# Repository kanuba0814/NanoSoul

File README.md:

# NanoSoul · ESP32-P4 桌面陪伴机器人

NanoSoul 是一台桌面陪伴机器人。它在本地检测人脸和环境，据此决定表情和动作；联网后可以进行语音对话。项目是团队参赛作品（2026 中国高校计算机大赛·人工智能创意赛），本仓库中的固件、测试上位机和文档由我提交。

当前实物是 **Waveshare ESP32-P4-WIFI6 开发板 + 现成模块 + 杜邦线**。

## 几个关键判断

- **实时决策不依赖云端。** 赛题要求主要功能运行在乐鑫芯片上，所以感知 → 决策 → 表情这条链全部在 ESP32-P4 本地完成：OV5647 → PPA 降采样 → ESP-DL 人脸检测 → 10 Hz、9 个状态的状态机。云端只负责深度对话，不进入决策环，因此断网时机器人照样能运转。
- **语音触发选能用的方案，而不是看起来高级的方案。** WakeNet9 和 MultiNet7 的模型加载和 AFE 管线都能跑，但在当前板载麦克风下口令检测不稳定。所以演示默认使用能量 VAD（检测到持续语音后才录音），再用 STT 文本判断是否包含唤醒词「小王」；神经网络方案保留为实验选项。
- **安全是硬需求，不是附加功能。** 电机堵转判定条件是 INA219 电流升高且编码器不动，触发后拉低 TB6612 的 STBY 急停；电机默认关闭，只有显式使能后才会驱动。
- **只有一块开发板，所以尽量把验证做在板外。** 共享脚本必须能在没有开发板的机器上运行；状态机、运动仲裁、堵转判定等逻辑都有板外自检（`soul_sim`、`arbiter`、`stall_sim` 等），上板后再用 SELFTEST 模式逐项确认。

## 验证状态

| 状态 | 内容 |
|---|---|
| ✅ 实物验证 | 本地人脸检测约 8 fps；480×640 屏幕动画表情约 30 fps；断网运行本地状态机；录音 → STT → LLM → TTS → 播放全链路（2026-07-08 打通，120 s 稳定性测试无 panic / WDT / reset）；WebSocket 上位机与测试模式 |
| 🟡 代码完成，只通过板外自检 | 三轮全向运动原语、堵转保护闭环、轮速闭环与里程计（校准记录尚未填写）；IMU、环境光组件需接线后实测 |
| ⬜ 未完成 | 外壳打印装配（目前只完成 SolidWorks 初步建模）、工具调用、OTA |

完整的功能清单和每一项的状态见 [`docs/00_成品全景与技术框架.md`](docs/00_成品全景与技术框架.md)。

## 开发方式

开发过程与 Claude Code 协作完成，约定写在 [`CLAUDE.md`](CLAUDE.md)：优先复用乐鑫官方组件，现成没有的由 AI 产出、人工复核；commit 前固件必须通过 `idf.py build`；AI 给出的接线、电平和上电顺序全部由人复核。

## 目录

```text
main/                 程序入口和板级驱动（电机、编码器、INA219）
components/           视觉、状态机（soul）、表情、运动、语音、联网、自检等组件
esp_emote_gen_player/ 乐鑫表情播放器（vendored）
spiffs_image/         表情资源包
sdcard_template/      SD 卡配置示例，不含真实密钥
tools/testhost/       浏览器测试上位机与诊断工具
enclosure/            SolidWorks 外壳源文件与导出
docs/                 系统说明、接口协议、引脚表和测试记录
```

## 编译与烧录

开发环境：ESP-IDF v5.5.2，目标芯片 ESP32-P4。

```bash
source $IDF_PATH/export.sh
idf.py set-target esp32p4
idf.py build
idf.py -p /dev/ttyACM0 flash monitor   # 需要连接开发板
```

SD 卡配置和上板自检见 [`docs/10_上板验证_SD配置与烧录.md`](docs/10_上板验证_SD配置与烧录.md)。复制 `sdcard_template/nanosoul/config.example.json` 到 SD 卡 `/nanosoul/config.json`，填写 Wi-Fi 和模型服务配置；真实密码和 API Key 不进仓库。

## 运行模式

- `FACE`：默认模式，运行表情、视觉、状态机、语音、联网和上位机服务。
- `SELFTEST`：循环运行整机自检，输出 JSON 结果。
- `TEST`：在完整运行时之上增加传感值注入、电机测试和串口协议；上电时 IO48 接地即可进入。浏览器上位机为 [`tools/testhost/index.html`](tools/testhost/index.html)，协议见 [`docs/13_测试模式与上位机_v1.md`](docs/13_测试模式与上位机_v1.md)。

## 硬件接线

开发板由 USB 供电，电池经 XL6009 升压后单独给电机供电，两路电源必须共地；电机干线走母排并星形接地，避免电机一转电机电源就被拉低到 1.3 V。引脚见 [`docs/BOARD_MAPPING.md`](docs/BOARD_MAPPING.md)，接线图见 [`docs/应急方案_无PCB/`](docs/应急方案_无PCB/)。

## 分支与标签

| 分支 / 标签 | 内容 |
|---|---|
| `main` | 当前整机固件 |
| `v1.0-submission` | 赛前提交时的验证版本 |
| `test` | 完整测试固件：全量组件、testhost 与工具链 |
| `test-host` | 测试上位机与公开版文档整理 |
| `soul-app` | 交互里程碑 M1–M8：自主行为、堵转保护、微动作 |
| `feat-p4-hw-baseline-from-testP4` | 从测试板迁移 P4 硬件基线的最早版本 |

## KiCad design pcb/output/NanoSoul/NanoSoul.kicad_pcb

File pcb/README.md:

# pcb/ — NanoSoul 载板（circuit-synth → KiCad 10）

代码优先：电路在 [`circuit/`](circuit/) 用 Python 描述，生成 KiCad 10 工程到 [`output/`](output/)。
真值源是 [`docs/02_硬件规格.md`](../docs/02_硬件规格.md) 与 [`docs/BOARD_MAPPING.md`](../docs/BOARD_MAPPING.md)。

## 环境（一次）

```fish
source scripts/setup.fish     # conda env nanosoul-eda(py3.12) + circuit-synth + easyeda2kicad + flatpak KiCad 库路径
scripts/fetch_libs.fish       # 按 LCSC 号下载真实符号/封装到 libs/（已含 ICM-42688/IP5306/TB6612/MT3608/DW01A/FS8205A/BH1750/SS34）
```

## 生成

```fish
scripts/generate.fish         # 跑 circuit/main.py → output/NanoSoul.* → ERC
```

## 关键约定

- **KiCad 是 flatpak**：命令行经 `bin/kicad-cli`（包了 `flatpak run --command=kicad-cli org.kicad.KiCad`）。
- **库解析**：`KICAD_SYMBOL_DIR` / `KICAD_FOOTPRINT_DIR` 用冒号分隔「flatpak 库存库 : 本项目 libs/」。circuit-synth 据此索引。
- **器件库不许占位符**：非库存件用 `easyeda2kicad --full --lcsc_id Cxxxx` 下载到 `libs/nanosoul.*`，符号名见 `circuit/pins.py` 顶部表。库存件（R/C/连接器/排针）用 KiCad 10 自带库。
- **首版止于**：原理图 + 网表 + 圆形板框(Ø≤110mm) + 粗布局 + 飞线。**关键/大电流走线人工在 KiCad 完成**（docs 铁律：关键板不赌 AI 自动布线）。
- **板框尺寸**：开发板真实 L×W/孔位/两排行距，从 Waveshare 官方 STEP/尺寸图 + 实板卡尺锁定后再定圆板框（见 `circuit/main.py` 顶部 TODO）。

## 与 docs 的关系

EDA 流程从嘉立创EDA 改为 circuit-synth→KiCad 10（决策见 docs/03 T-008、docs/04 D-016）。嘉立创仍用于打样/制造与 LCSC 选型。

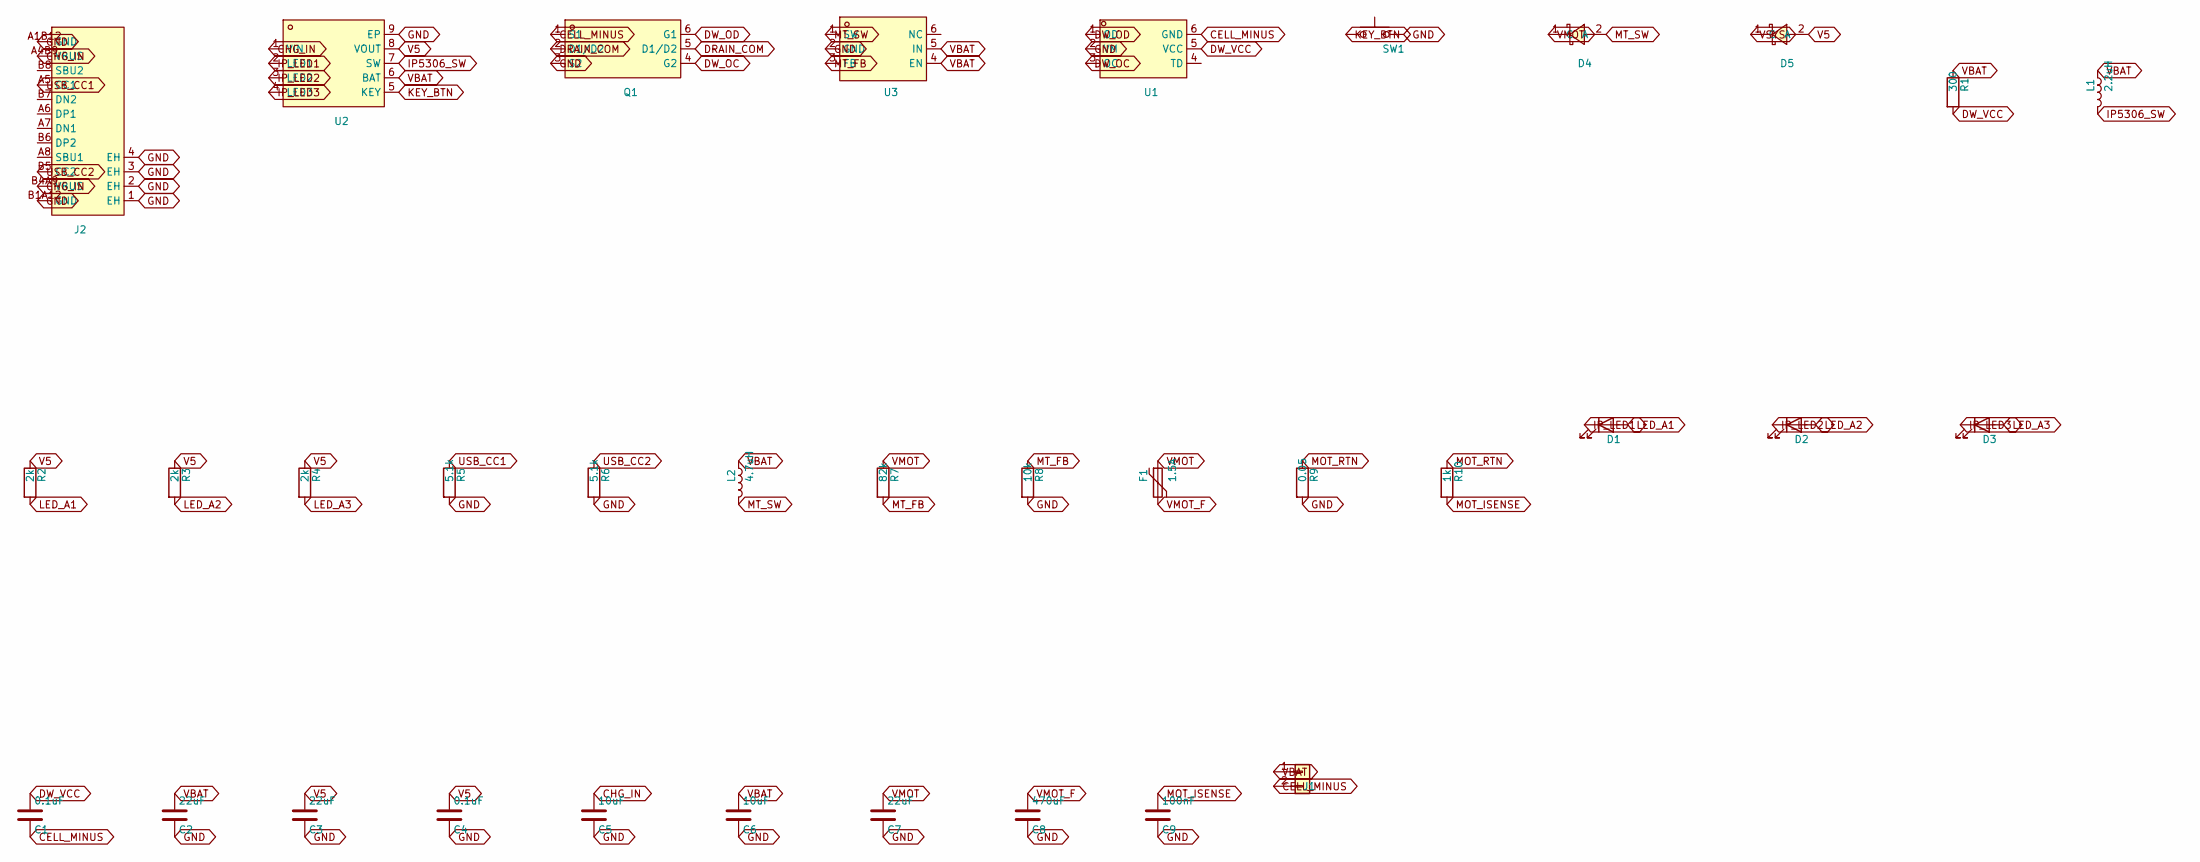
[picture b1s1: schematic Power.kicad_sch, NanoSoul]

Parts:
C1, C4: 0.1uF; C_0603_1608Metric
C2, C3, C7: 22uF; C_0805_2012Metric
C5, C6: 10uF; C_0805_2012Metric
C8: 470uF; CP_Elec_8x10.5
C9: 100nF; C_0603_1608Metric
D1, D2, D3: LED_0805_2012Metric
D4, D5: SMA_L4.3-W2.7-LS5.1-RD
F1: 1.5A; Fuse_0805_2012Metric
J1: JST_PH_B2B-PH-K_1x02_P2.00mm_Vertical
J2: USB-C_SMD-TYPE-C-31-M-12_1
L1: 2.2uH; L_6.3x6.3_H3
L2: 4.7uH; L_6.3x6.3_H3
Q1: SOT-23-6_L2.9-W1.6-P0.95-LS2.8-BR
R1: 300; R_0603_1608Metric
R2, R3, R4: 2k; R_0603_1608Metric
R5, R6: 5.1k; R_0603_1608Metric
R7: 82k; R_0603_1608Metric
R8: 10k; R_0603_1608Metric
R9: 0.05; R_1206_3216Metric
R10: 1k; R_0603_1608Metric
SW1: SW_SPST_CK_RS282G05A3
U1, U3: SOT-23-6_L2.9-W1.6-P0.95-LS2.8-BL
U2: ESOP-8_L4.9-W3.9-P1.27-LS6.0-BL-EP2.0

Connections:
CELL_MINUS: C1.2, J1.2, Q1.1 (S1), U1.6 (GND)
CHG_IN: C5.1, J2.A4B9 (VBUS), J2.B4A9 (VBUS), U2.1 (VIN)
DRAIN_COM: Q1.2 (D1/D2), Q1.5 (D1/D2)
DW_OC: Q1.4 (G2), U1.3 (OC)
DW_OD: Q1.6 (G1), U1.1 (OD)
DW_VCC: C1.1, R1.2, U1.5 (VCC)
GND: C2.2, C3.2, C4.2, C5.2, C6.2, C7.2, C8.2, C9.2, J2.1 (EH), J2.2 (EH), J2.3 (EH), J2.4 (EH), J2.A1B12 (GND), J2.B1A12 (GND), Q1.3 (S2), R5.2, R6.2, R8.2, R9.2, SW1.2, U1.2 (VM), U2.9 (EP), U3.2 (GND); also elsewhere on the board
IP5306_SW: L1.2, U2.7 (SW)
IP_LED1: D1.1 (K), U2.2 (LED1)
IP_LED2: D2.1 (K), U2.3 (LED2)
IP_LED3: D3.1 (K), U2.4 (LED3)
KEY_BTN: SW1.1, U2.5 (KEY)
LED_A1: D1.2 (A), R2.2
LED_A2: D2.2 (A), R3.2
LED_A3: D3.2 (A), R4.2
MOT_ISENSE: C9.1, R10.2; also elsewhere on the board
MOT_RTN: R9.1, R10.1; also elsewhere on the board
MT_FB: R7.2, R8.1, U3.3 (FB)
MT_SW: D4.2 (A), L2.2, U3.1 (SW)
USB_CC1: J2.A5 (CC1), R5.1
USB_CC2: J2.B5 (CC2), R6.1
V5: C3.1, C4.1, D5.2 (A), R2.1, R3.1, R4.1, U2.8 (VOUT)
VBAT: C2.1, C6.1, J1.1, L1.1, L2.1, R1.1, U2.6 (BAT), U3.4 (EN), U3.5 (IN)
VMOT: C7.1, D4.1 (C), F1.1, R7.1
VMOT_F: C8.1, F1.2; also elsewhere on the board
VSYS: D5.1 (C); also elsewhere on the board

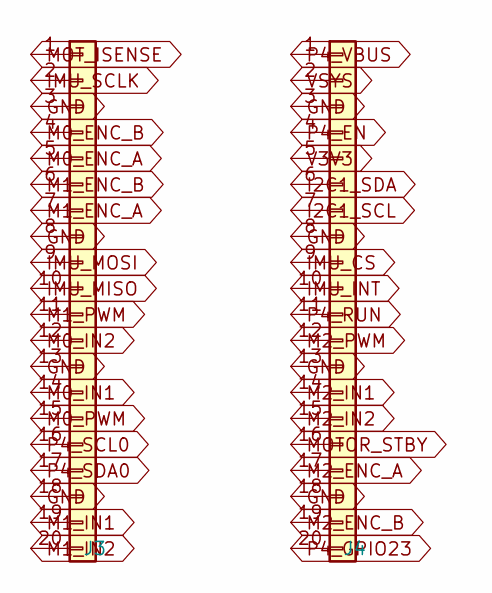
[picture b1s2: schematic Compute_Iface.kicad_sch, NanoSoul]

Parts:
J3, J4: PinSocket_1x20_P2.54mm_Vertical

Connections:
GND: J3.3, J3.8, J3.13, J3.18, J4.3, J4.8, J4.13, J4.18; also elsewhere on the board
I2C1_SCL: J4.7; also elsewhere on the board
I2C1_SDA: J4.6; also elsewhere on the board
IMU_CS: J4.9; also elsewhere on the board
IMU_INT: J4.10; also elsewhere on the board
IMU_MISO: J3.10; also elsewhere on the board
IMU_MOSI: J3.9; also elsewhere on the board
IMU_SCLK: J3.2; also elsewhere on the board
M0_ENC_A: J3.5; also elsewhere on the board
M0_ENC_B: J3.4; also elsewhere on the board
M0_IN1: J3.14; also elsewhere on the board
M0_IN2: J3.12; also elsewhere on the board
M0_PWM: J3.15; also elsewhere on the board
M1_ENC_A: J3.7; also elsewhere on the board
M1_ENC_B: J3.6; also elsewhere on the board
M1_IN1: J3.19; also elsewhere on the board
M1_IN2: J3.20; also elsewhere on the board
M1_PWM: J3.11; also elsewhere on the board
M2_ENC_A: J4.17; also elsewhere on the board
M2_ENC_B: J4.19; also elsewhere on the board
M2_IN1: J4.14; also elsewhere on the board
M2_IN2: J4.15; also elsewhere on the board
M2_PWM: J4.12; also elsewhere on the board
MOTOR_STBY: J4.16; also elsewhere on the board
MOT_ISENSE: J3.1; also elsewhere on the board
P4_EN: J4.4
P4_GPIO23: J4.20
P4_RUN: J4.11
P4_SCL0: J3.16
P4_SDA0: J3.17
P4_VBUS: J4.1
V3V3: J4.5; also elsewhere on the board
VSYS: J4.2; also elsewhere on the board

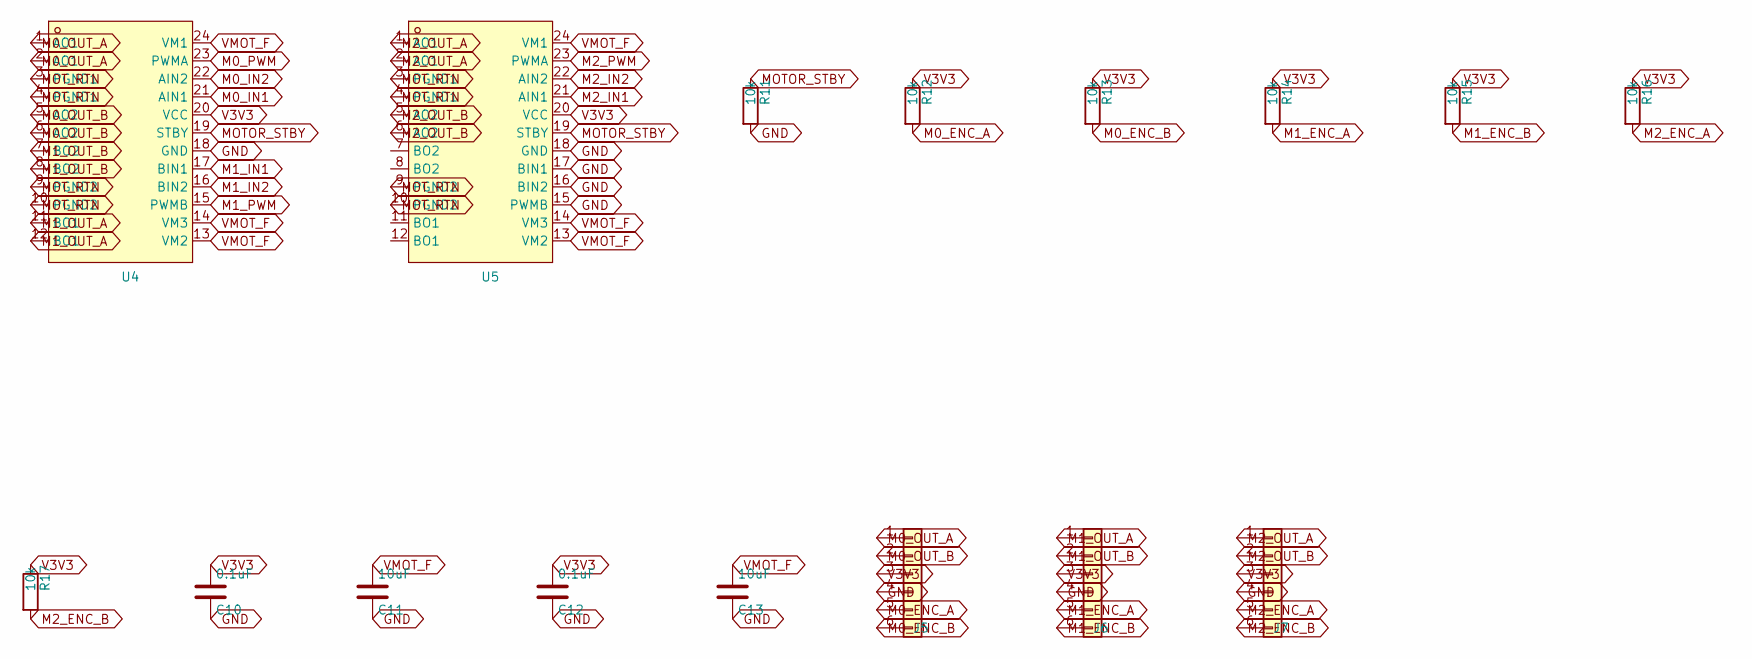
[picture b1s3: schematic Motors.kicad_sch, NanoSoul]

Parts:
C10, C12: 0.1uF; C_0603_1608Metric
C11, C13: 10uF; C_0805_2012Metric
J5, J6, J7: PinHeader_1x06_P2.54mm_Vertical
R11, R12, R13, R14, R15, R16, R17: 10k; R_0603_1608Metric
U4, U5: SSOP-24_L8.3-W5.6-P0.65-LS7.6-BL

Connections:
GND: C10.2, C11.2, C12.2, C13.2, J5.4, J6.4, J7.4, R11.2, U4.18 (GND), U5.15 (PWMB), U5.16 (BIN2), U5.17 (BIN1), U5.18 (GND); also elsewhere on the board
M0_ENC_A: J5.5, R12.2; also elsewhere on the board
M0_ENC_B: J5.6, R13.2; also elsewhere on the board
M0_IN1: U4.21 (AIN1); also elsewhere on the board
M0_IN2: U4.22 (AIN2); also elsewhere on the board
M0_OUT_A: J5.1, U4.1 (AO1), U4.2 (AO1)
M0_OUT_B: J5.2, U4.5 (AO2), U4.6 (AO2)
M0_PWM: U4.23 (PWMA); also elsewhere on the board
M1_ENC_A: J6.5, R14.2; also elsewhere on the board
M1_ENC_B: J6.6, R15.2; also elsewhere on the board
M1_IN1: U4.17 (BIN1); also elsewhere on the board
M1_IN2: U4.16 (BIN2); also elsewhere on the board
M1_OUT_A: J6.1, U4.11 (BO1), U4.12 (BO1)
M1_OUT_B: J6.2, U4.7 (BO2), U4.8 (BO2)
M1_PWM: U4.15 (PWMB); also elsewhere on the board
M2_ENC_A: J7.5, R16.2; also elsewhere on the board
M2_ENC_B: J7.6, R17.2; also elsewhere on the board
M2_IN1: U5.21 (AIN1); also elsewhere on the board
M2_IN2: U5.22 (AIN2); also elsewhere on the board
M2_OUT_A: J7.1, U5.1 (AO1), U5.2 (AO1)
M2_OUT_B: J7.2, U5.5 (AO2), U5.6 (AO2)
M2_PWM: U5.23 (PWMA); also elsewhere on the board
MOTOR_STBY: R11.1, U4.19 (STBY), U5.19 (STBY); also elsewhere on the board
MOT_RTN: U4.3 (PGND1), U4.4 (PGND1), U4.9 (PGND2), U4.10 (PGND2), U5.3 (PGND1), U5.4 (PGND1), U5.9 (PGND2), U5.10 (PGND2); also elsewhere on the board
V3V3: C10.1, C12.1, J5.3, J6.3, J7.3, R12.1, R13.1, R14.1, R15.1, R16.1, R17.1, U4.20 (VCC), U5.20 (VCC); also elsewhere on the board
VMOT_F: C11.1, C13.1, U4.13 (VM2), U4.14 (VM3), U4.24 (VM1), U5.13 (VM2), U5.14 (VM3), U5.24 (VM1); also elsewhere on the board

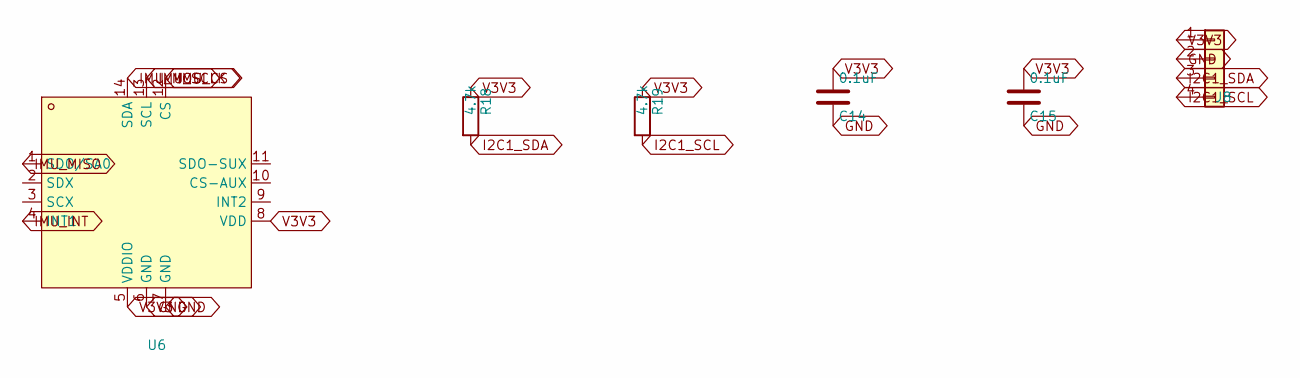
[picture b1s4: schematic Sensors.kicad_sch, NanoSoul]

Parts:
C14, C15: 0.1uF; C_0603_1608Metric
J8: JST_SH_BM04B-SRSS-TB_1x04-1MP_P1.00mm_Vertical
R18, R19: 4.7k; R_0603_1608Metric
U6: LGA-14_L3.0-W2.5-P0.50-BR

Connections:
GND: C14.2, C15.2, J8.2, U6.6 (GND), U6.7 (GND); also elsewhere on the board
I2C1_SCL: J8.4, R19.2; also elsewhere on the board
I2C1_SDA: J8.3, R18.2; also elsewhere on the board
IMU_CS: U6.12 (CS); also elsewhere on the board
IMU_INT: U6.4 (INT1); also elsewhere on the board
IMU_MISO: U6.1 (SDO/SA0); also elsewhere on the board
IMU_MOSI: U6.14 (SDA); also elsewhere on the board
IMU_SCLK: U6.13 (SCL); also elsewhere on the board
V3V3: C14.1, C15.1, J8.1, R18.1, R19.1, U6.5 (VDDIO), U6.8 (VDD); also elsewhere on the board

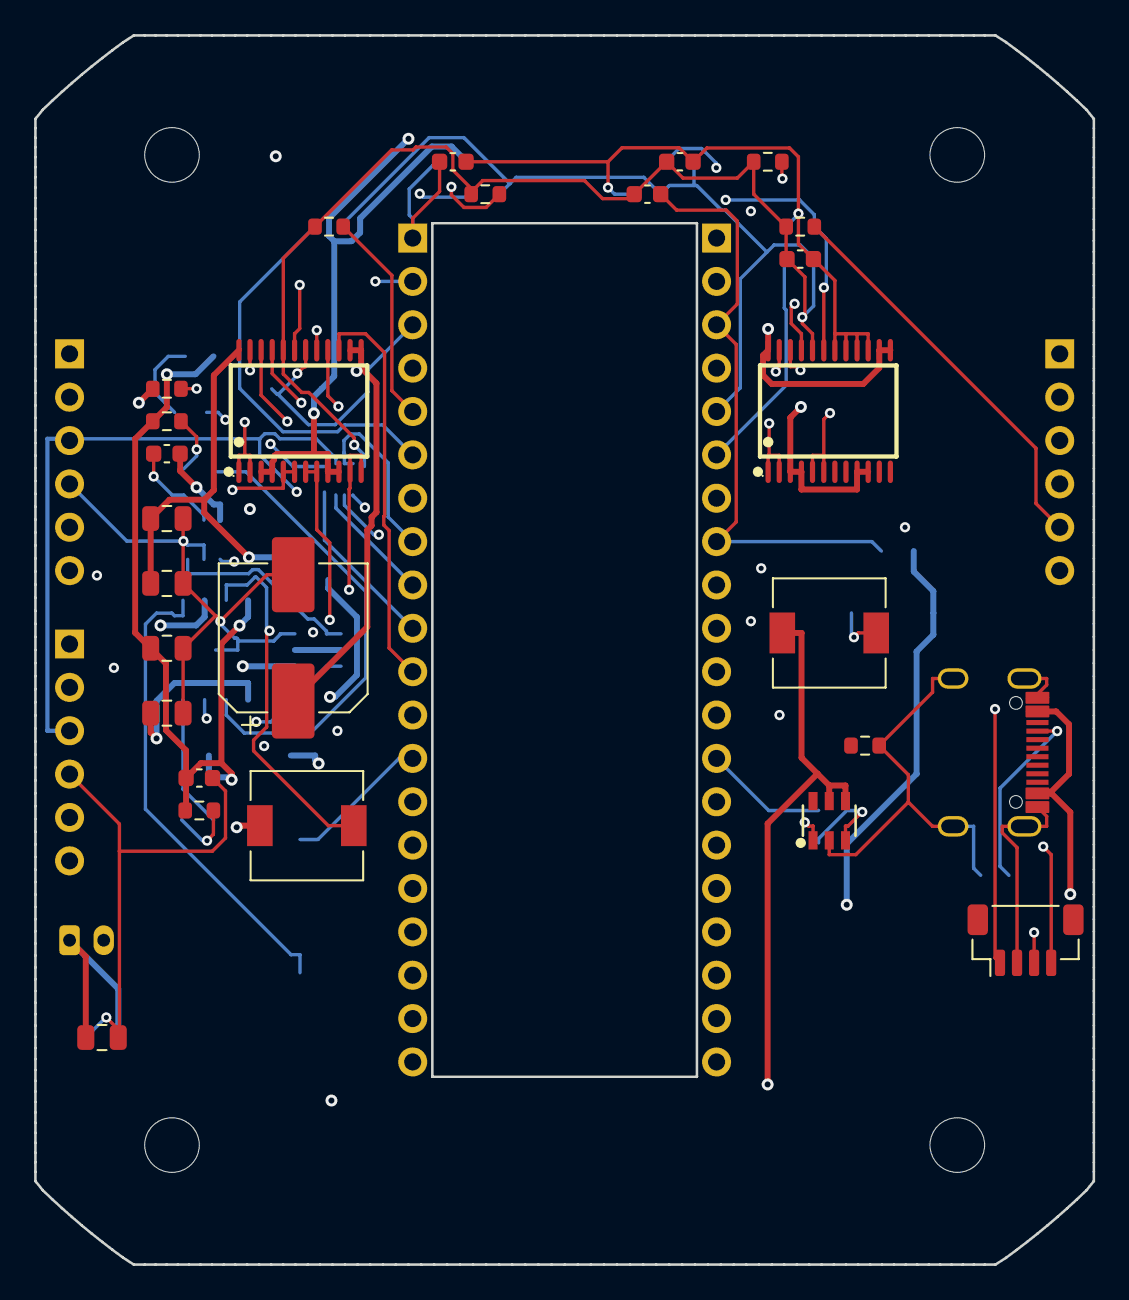
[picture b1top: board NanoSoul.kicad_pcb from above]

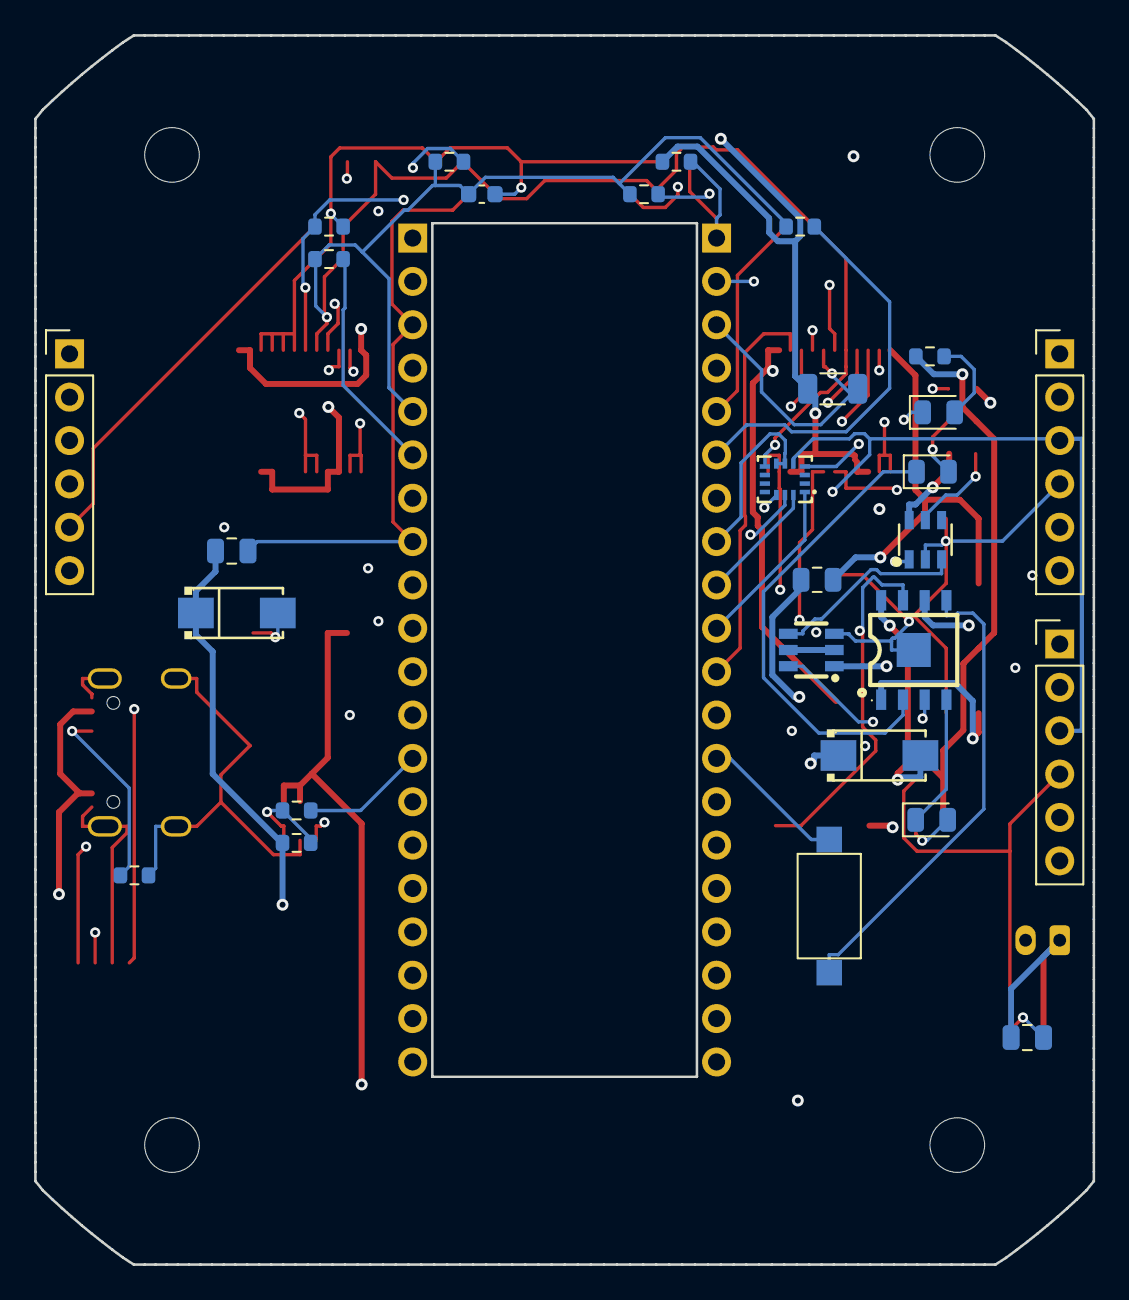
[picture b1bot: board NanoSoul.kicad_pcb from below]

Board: 4 copper layers, 62.0 x 72.0 mm, 62 parts (28 on the bottom side), 56 nets.

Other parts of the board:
H1, H2, H3, H4: MountingHole_3.2mm_M3

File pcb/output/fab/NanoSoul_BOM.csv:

Comment,Designator,Footprint,LCSC Part #,类型/备注
0.1uF,"C1,C4,C10,C12,C14,C15",0603,C14663,SMD
100nF,C9,0603,C14663,SMD
10k,"R8,R11,R12,R13,R14,R15,R16,R17",0603,C25804,SMD
1k,R10,0603,C21190,SMD
2k,"R2,R3,R4",0603,C22975,SMD
300,R1,0603,C23025,SMD
4.7k,"R18,R19",0603,C23162,SMD
5.1k,"R5,R6",0603,C23186,SMD
82k,R7,0603,C23254,SMD
1.5A,F1,0805,C207025,SMD
10uF,"C5,C6,C11,C13",0805,C15850,SMD
22uF,"C2,C3,C7",0805,C45783,SMD
LED 红 0805,"D1,D2,D3",0805,C84256,SMD｜极性/旋转核对
0.05,R9,1206,C375525,SMD
470uF,C8,CP_8x10.5,C4747956,SMD｜极性/旋转核对
IP5306 (I2C版),U2,ESOP-8,C488349,SMD｜极性/旋转核对
2.2uH SWPA6045S2R2NT,L1,Inductor_6.3x6.3,C36500,SMD
4.7uH SWPA6045S4R7MT,L2,Inductor_6.3x6.3,C78804,SMD
,J1,JST-PH 2P,C131337,THT 插件
,J8,JST-SH 4P,C495539,SMD
QMI8658A,U6,LGA-14,C3021082,SMD｜极性/旋转核对
SS34,"D4,D5",SMA(DO-214AC),C908680,SMD｜极性/旋转核对
DW01A,U1,SOT-23-6,C351410,SMD｜极性/旋转核对
FS8205A,Q1,SOT-23-6,C908265,SMD｜极性/旋转核对
MT3608,U3,SOT-23-6,C84817,SMD｜极性/旋转核对
TB6612FNG,"U4,U5",SSOP-24,C141517,SMD｜极性/旋转核对
,J2,USB-C_SMD-TYPE-C-31-M-12_1,C165948,SMD｜极性/旋转核对
轻触开关 TS-1088 2P,SW1,轻触开关,C720477,SMD
,"J5,J6,J7",排针 1x06 2.54,,THT 插件
,"J3,J4",母座 1x20 2.54,,THT 插件

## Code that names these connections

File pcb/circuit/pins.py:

"""共享网名、开发板排针映射、器件符号/封装常量。

真值源 = docs/BOARD_MAPPING.md。改引脚先改那里再改这里。

器件符号/封装（来自 pcb/libs/nanosoul.*，easyeda2kicad 按 LCSC 号下载）：
  QMI8658A        symbol nanosoul:QMI8658C             fp nanosoul:LGA-14_L3.0-W2.5-P0.50-BR  (下单 C3021082；C 版 C2842151 在 JLC SMT 停产/邮寄→换同族 A 版，脚位/驱动一致，见 docs/06)
  TYPE-C-31-M-12  symbol nanosoul:TYPE-C-31-M-12       fp nanosoul:USB-C_SMD-TYPE-C-31-M-12_1 (C165948，板上充电口)
  IP5306-I2C      symbol nanosoul:IP5306-I2C           fp nanosoul:ESOP-8_L4.9-W3.9-P1.27-LS6.0-BL-EP2.0
  TB6612FNG       symbol "nanosoul:TB6612FNG,C,8,EL"   fp nanosoul:SSOP-24_L8.3-W5.6-P0.65-LS7.6-BL
  MT3608          symbol nanosoul:MT3608               fp nanosoul:SOT-23-6_L2.9-W1.6-P0.95-LS2.8-BL
  DW01A           symbol nanosoul:DW01A_C351410        fp nanosoul:SOT-23-6_L2.9-W1.6-P0.95-LS2.8-BL
  FS8205A         symbol nanosoul:FS8205A_C908265      fp nanosoul:SOT-23-6_L2.9-W1.6-P0.95-LS2.8-BR
  BH1750FVI       symbol nanosoul:BH1750FVI-TR         fp nanosoul:WSOF-6_L2.6-W1.6-P0.50-TL-EP
  SS34            symbol nanosoul:SS34_C908680         fp nanosoul:SMA_L4.3-W2.7-LS5.1-RD
"""

# ---- 器件符号 ----
SYM_IMU = "nanosoul:QMI8658C"          # 脚位同 QMI8658A(实下单件，C 版 JLC 停产)；4 线 SPI，见 sensors.py / docs/06
SYM_USBC = "nanosoul:TYPE-C-31-M-12"   # 板上充电口（C165948）；footprint 已修(NPTH 机械孔 + 收窄合并盘描边)
SYM_IP5306 = "nanosoul:IP5306-I2C"
SYM_TB6612 = "nanosoul:TB6612FNG,C,8,EL"
SYM_MT3608 = "nanosoul:MT3608"
SYM_DW01 = "nanosoul:DW01A_C351410"
SYM_FS8205 = "nanosoul:FS8205A_C908265"
SYM_BH1750 = "nanosoul:BH1750FVI-TR"
SYM_SS34 = "nanosoul:SS34_C908680"

# ---- 器件封装 ----
FP_IMU = "nanosoul:LGA-14_L3.0-W2.5-P0.50-BR"      # QMI8658C，与 ICM 同 LGA-14 外形
FP_USBC = "nanosoul:USB-C_SMD-TYPE-C-31-M-12_1"
FP_IP5306 = "nanosoul:ESOP-8_L4.9-W3.9-P1.27-LS6.0-BL-EP2.0"
FP_TB6612 = "nanosoul:SSOP-24_L8.3-W5.6-P0.65-LS7.6-BL"
FP_MT3608 = "nanosoul:SOT-23-6_L2.9-W1.6-P0.95-LS2.8-BL"
FP_DW01 = "nanosoul:SOT-23-6_L2.9-W1.6-P0.95-LS2.8-BL"
FP_FS8205 = "nanosoul:SOT-23-6_L2.9-W1.6-P0.95-LS2.8-BR"
FP_BH1750 = "nanosoul:WSOF-6_L2.6-W1.6-P0.50-TL-EP"
FP_SS34 = "nanosoul:SMA_L4.3-W2.7-LS5.1-RD"

# ---- 库存封装 ----
FP_R0603 = "Resistor_SMD:R_0603_1608Metric"
FP_R0805 = "Resistor_SMD:R_0805_2012Metric"
FP_R1206 = "Resistor_SMD:R_1206_3216Metric"        # R9 电流采样 shunt：0805 50mΩ 在 JLC 无现货 → 1206(C375525 有货 15k/250mW)
FP_C0603 = "Capacitor_SMD:C_0603_1608Metric"
FP_C0805 = "Capacitor_SMD:C_0805_2012Metric"
FP_CE_D8 = "Capacitor_SMD:CP_Elec_8x10.5"          # 电解 bulk
FP_L_12x12 = "Inductor_SMD:L_6.3x6.3_H3"            # boost 电感（6.3×6.3 SMD 功率电感）
FP_LED0805 = "LED_SMD:LED_0805_2012Metric"
FP_HDR_1x20 = "Connector_PinSocket_2.54mm:PinSocket_1x20_P2.54mm_Vertical"  # 母座：开发板插入
FP_HDR_1x06 = "Connector_PinHeader_2.54mm:PinHeader_1x06_P2.54mm_Vertical"
FP_HDR_1x02 = "Connector_PinHeader_2.54mm:PinHeader_1x02_P2.54mm_Vertical"
FP_JST_PH2 = "Connector_JST:JST_PH_B2B-PH-K_1x02_P2.00mm_Vertical"
FP_JST_SH4 = "Connector_JST:JST_SH_BM04B-SRSS-TB_1x04-1MP_P1.00mm_Vertical"
FP_SW_PUSH = "Button_Switch_SMD:SW_SPST_CK_RS282G05A3"
FP_POLY0805 = "Fuse:Fuse_0805_2012Metric"

# ---- 全部需要的网名（GND 单独）----
# 电源轨
RAILS = [
    "VBAT",        # 电池正（保护后）= 系统电池轨
    "CELL_MINUS",  # 电芯负（保护 MOS 之间）
    "DRAIN_COM",   # FS8205A 公共漏
    "V5",          # IP5306 5V 输出
    "VSYS",        # 注入开发板的 5V（经 SS34）
    "V3V3",        # 开发板回灌 3V3（传感器轨）
    "VMOT",        # MT3608 升压输出
    "VMOT_F",      # 经 PTC 后给 TB6612 VM
    "MOT_RTN",     # 电机回流（低边采流节点）
    "CHG_IN",      # 充电口 5V → IP5306 VIN
    "IP5306_SW",   # IP5306 电感节点
    "MT_SW",       # MT3608 电感节点
    "MT_FB",       # MT3608 反馈
    "KEY_BTN",     # IP5306 按键
    "IP_LED1", "IP_LED2", "IP_LED3",
]
# 运动/编码器/IMU/I2C/ADC 信号
SIGNALS = [
    "M0_PWM", "M0_IN1", "M0_IN2", "M1_PWM", "M1_IN1", "M1_IN2",
    "M2_PWM", "M2_IN1", "M2_IN2", "MOTOR_STBY",
    "M0_ENC_A", "M0_ENC_B", "M1_ENC_A", "M1_ENC_B", "M2_ENC_A", "M2_ENC_B",
    "M0_OUT_A", "M0_OUT_B", "M1_OUT_A", "M1_OUT_B", "M2_OUT_A", "M2_OUT_B",
    "IMU_SCLK", "IMU_MOSI", "IMU_MISO", "IMU_CS", "IMU_INT",
    "I2C1_SDA", "I2C1_SCL", "MOT_ISENSE",
]
# 开发板侧透传/备用（仅出现在母排上）
PASSTHRU = ["P4_VBUS", "P4_EN", "P4_RUN", "P4_SDA0", "P4_SCL0", "P4_GPIO23"]

# ---- 母排逐脚映射（"GND" 表示接地）----
# 与板上分区协同：左排 J3 = 左月牙(M0/M1 电机 + IMU)；右排 J4 = 右月牙(M2 + 光照 I²C1)。
# 使每个信号的母排脚就在它所连器件那一侧 → 接线最短、少跨中线。
# 左排 J3（datasheet 丝印 上→下 = pin 1..20；GPIO 顺序 52,51,-,31,30,29,28,-,50,49,5,4,-,3,2,8,7,-,24,25）
# pin1=IO52 放 MOT_ISENSE（ADC2_CH3）：IO33 无 ADC，MOT_ISENSE 从这里取（shunt 在左月牙、就近）。
LEFT_HDR = [
    "MOT_ISENSE", "IMU_SCLK", "GND", "M0_ENC_B", "M0_ENC_A", "M1_ENC_B", "M1_ENC_A", "GND",
    "IMU_MOSI", "IMU_MISO", "M1_PWM", "M0_IN2", "GND", "M0_IN1", "M0_PWM", "P4_SCL0",
    "P4_SDA0", "GND", "M1_IN1", "M1_IN2",
]
# 右排 J4（上→下；GPIO 顺序 VBUS,VSYS,-,EN,3V3,20,21,-,22,23,RUN,26,-,27,32,33,46,-,47,48）
# ADC 修正(ESP32-P4 datasheet 复核)：IO33 无 ADC（ADC1=IO16-23/ADC2=IO49-54）→ MOT_ISENSE 移到 IO52(ADC2_CH3)，
# 把纯数字的 MOTOR_STBY 放 IO33(pin16)：旁边就是右月牙 U5(TB6612#2) STBY 脚，有就近锚点好布；IMU 五脚全留原位。
RIGHT_HDR = [
    "P4_VBUS", "VSYS", "GND", "P4_EN", "V3V3", "I2C1_SDA", "I2C1_SCL", "GND",
    "IMU_CS", "IMU_INT", "P4_RUN", "M2_PWM", "GND", "M2_IN1", "M2_IN2", "MOTOR_STBY",
    "M2_ENC_A", "GND", "M2_ENC_B", "P4_GPIO23",
]

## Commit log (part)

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2026-04-19 Initial repository scaffold
2026-04-19 readme
2026-04-19 硬件文档完全定义与README小更新
2026-04-19 Add team ownership split to README
2026-04-19 添加乐鑫文档mcp设置
2026-04-19 中文化README
2026-04-19 /init
2026-04-19 README tops
2026-04-20 claude md commit
2026-04-22 更新了框架，现在更适合烧烤
2026-04-26 chore: checkpoint scaffold before p4 hardware migration
2026-04-26 feat: migrate p4 hardware baseline from testP4
2026-05-07 烧烤了设定文档，掉了一些token
2026-06-20 backup: 工作区首版（固件骨架 + circuit-synth/KiCad 载板 + 已自动布线的 PCB）
    备份点：含用户在 KiCad 里自动布线后的 NanoSoul.kicad_pcb（1147 段+106 过孔），
    便于后续补线/改动前回退。
2026-06-21 pcb: 3mm 白边 + J2/J7 离 J4 + DRC 丝印告警清零
    - 最外围 3mm 白边：板放大到 94×92（Ø108 切边收小到 7/8mm），铜/器件焊盘距最外缘 ≥3mm
    （自动布线内缩 3mm；顶排 J5/J6 下移、J8 左移退出白边区）。
    - J2/J7 离 J4：右月牙整体右移 1.6mm，离 J4 本体 +0.83mm（原相擦 0.78mm）。
    - DRC = 0 warning：5 个位号(D4/D5/Q1/U1/U7)挪开、接线图例升到 0.8mm 并缩短、
    删 J3/J4 压挖孔丝印、隐藏 6 安装孔与 U7 位号。
    - 17.8mm 母座行距核对通过；4 个 M3 安装孔成规则 54×82 矩形（旧版钉在 Ø108 圆外、钻不出，已修正）。
2026-06-21 erc: 按 circuit-synth 网表为真值源的流程配置 ERC + 核对网表连通
    - 开源版 circuit-synth 原理图导出无导线（5 张子图 wire=0），KiCad ERC 217 条全是
    「无导线导出」工件，非设计错。已核对 .net 网表：57 器件/60 网，54 个多节点网全连通
    （GND=44 MOT_RTN=10 VMOT_F=10，电机/IMU/I²C 网节点数都对），6 个单节点是未用开发板脚（预期）。
    - 据此把那几类导出工件（pin_not_connected/pin_to_pin/hier_label_mismatch/label_dangling/
    power_pin_not_driven/multiple_net_names 等）在 .kicad_pro 置 ignore → ERC 报告 0。
    - docs/05 §9.1 记录原委与「网表为真值源」的判断。
2026-06-21 pcb: 自写迷宫布线补通 MOT_RTN/GND → PCB 0 未连 / 0 DRC
    - Freerouting 留空的 2 条跨挖孔大电流网/地（两端被母座+月牙器件夹死），用带净空校验的
    双层迷宫布线器(route2.py)布通：多源 BFS + 端点吸附/打过孔 + 守 3mm 白边 + 绕挖孔。
    - 复核：kicad-cli pcb drc = 0 violations / 0 unconnected；新铜距外缘 ≥3mm（5mm）。
    - 至此：PCB DRC 0、原理图 ERC 0（网表为真值源已核对）、3mm 白边、J2/J7 离 J4、17.8 行距 全过。
    - MOT_RTN 暂 0.5mm，载大电流前在 GUI 加宽；docs/05 §9.1 更新。
2026-06-22 pcb: 料号确认补全 + SW1 换 C720477 + 电机轨 5.5V / DRC 0 ERC 0
    待确认料号(report.xlsx)逐项查实并填进 fab BOM/CPL：
    - C8→C4747956（原写 RYVP25V470UF8*10 查无此件，换 25V/470µF/8×10.5）
    - L1→C2047296 / L2→C703091（LQH66SN 本体 6.3×6.3 与焊盘对得上；库存薄）
    - J1→C131337 / J8→C495539(TBT版) / D1-3→C84256(红0805) / F1→C207025(0805L150)
    - U2 C488349(认准 I²C 版) / U4U5 C141517(别买 C88224) 复核照原
    板子改动并复验：
2026-06-22 docs: 加无PCB应急方案 SKU BOM（模块清单+接线图+电气验证+电池参数）
    PCB 万一来不及打样/装配的后备方案：现成模块 + 杜邦线 + 绝缘胶带手工搭。
    含：
    - 模块级采购表（淘宝关键词+行情价，立创无成品模块故不编 LCSC C 号）+ 选购防买错提示
    - 详细接线图（graphviz 自动布局，每根箭头标引脚 IOxx→模块脚，竖版可读）
    - 电气验证：电压兼容/功率电流预算/续航/I²C 地址/GPIO 预算 + ngspice 实仿 I²C 长线上升时间
    - 电池详细参数（按整机峰值~3A 选 C 率，低 C 会压降掉电）
2026-06-23 docs: 按实物模块细化应急方案接线图 + 下单前必须定清单
    收到实物模块照片，逐一核对并细化：
    - IMU 实际是 QMI8658（走 I²C，非 ICM 的 SPI）→ 图改挂 I²C1 总线(SDA/SCL/INT→IO23/ADO定址)，SPI 脚释放
    - TP4056 二合一(充电+保护)→ 省掉单独 1S 保护板；电池 B+/B−，OUT+/OUT−=VBAT
    - 加总开关(≥3A，串 OUT+) + INA219 绿端子串电机轨 + MAX17048 VLogic→3V3/Bat→电池+
    - 接线图按实物重画：电源链/双升压/I²C总线/电机/编码器，每根箭头标引脚，连接核对无误
    新增「下单前必须定」清单（一次买齐别漏）：
2026-06-25 docs: 应急方案改「电脑供开发板/电池只带电机」架构，重画接线图(+共地)
    按实际决定调整供电架构：
    - 开发板改由电脑 USB 供电（独立一路，不碰电池）
    - 电池只经 XL6009 升 5.5V 带电机；电池从 TP4056 Type-C 口外部充电
    - 这套绕开了原全电池方案最大的两个风险（开发板升压扛不住 WiFi6 峰值掉电、整机~3.5A 触发 TP4056 过流跳闸）→ 不再需要 TPS61088/大 BMS
    接线图重画（graphviz，每根箭头标引脚）：
    - 两套独立电源画清；★强调 GND 必须共地(电脑地↔电池地)，否则 TB6612 信号/I²C 全失效
2026-06-25 docs: 应急方案加「安全装机/上电流程」防烧件章节
    新增一节，防止装配/上电时烧任何一个零件：
    - 防烧 7 条铁律（XL6009 空载先调 5.5V 再接负载=最致命一条、断电接线、VM≠VCC、
    MAX17048 VLogic≠电池、传感器只接 3V3、上电前查短路、第一次上电手放开关）
    - 上电前万用表检查（VCC/GND/极性目检 + 电池+/3V3/5.5V 对 GND 不短路 + 共地确认）
    - 分阶段上电 5 步（调压→开发板→共地→传感器逐个I²C验→最后接电机驱动悬空小占空比试）
    - 每个件「烧的原因→怎么防」表（TB6612/开发板I²C脚/传感器/电池/XL6009/电机）
2026-06-25 docs: 应急方案加「备用套装/保险包」(按风险点整理,跟主单一起下)
    就一个发货周期，按"最易烧/最易搞错/消耗快"整理备件，每件对到具体风险：
    - ① 易烧主力件直接备：TB6612×2(最易烧)、QMI8658/BH1750/INA219 各1、N20编码电机×1、XL6009×1、开关/TP4056
    - ② 主动保护小件(更难烧)：I²C 电平转换模块(救开发板I²C脚)、自恢复/玻璃管保险丝(电池短路兜底)、470/1000µF bulk电容、电阻包、肖特基
    - ③ 替代件(主件不行顶上)：DRV8833、LSM6DSO、SX1308/MT3608、杜邦线×2套、PH2.0+XH2.54端子线、热缩管
    - 提醒：开发板不可备→电平转换模块专护其I²C；
2026-06-25 docs: 备用套装 IMU 换便宜款 MPU6050 + 保险丝给具体参数
    - IMU 替代备件 LSM6DSO(¥12) → MPU6050/GY-521(¥3~8)：便宜、ESP-IDF 例程最多；
    注明缺点(老/漂移/无硬件Tap,碰撞抬起靠固件算) + ①已备同款 QMI8658 为首选备用
    - 保险丝补具体参数表(串电池正极)：额定电流 玻璃管 T3.15A~4A 慢断 / PTC Ihold≈3A·Itrip≈6A；
    额定电压 ≥6V；分断 ≥35A；5×20mm+座；T3.15A与T4A各备3~5
2026-06-25 docs+CLAUDE: 加实物电机/编码器参数+控制，CLAUDE.md 转向无PCB ESP-IDF 编程
    实物电机到手(N20 6V/118:1/136rpm/短轴D3×8)，完善接线图与控制：
    - 电机参数表(空载40/负载90/堵转400mA·个 → 3全堵才1.2A，预算很宽松)
    - 编码器 6 线颜色接法(红白=电机±、黑蓝=编码器±、黄绿=A/B)
    - ⚠️厂商两条硬要求：① 集电极开漏 → A/B 必须加上拉(内部上拉或10k到3V3,非5V)；
    ② 电机电源≠编码器电源(电机走TB6612/5.5V、编码器走3V3,共地即可)
    - 编码器分辨率 7PPR×118=826/相 ×4=3304计数/圈 → PCNT 正交；速度/里程公式
2026-06-26 docs: 编码器电机接法详解(单电机图解+方向一致性/消噪/上拉/连接器)
    - 加「单个电机怎么接」专图：N20 6 线分头接 TB6612(红白)/3V3(黑)/GND(蓝)/IO(黄绿)
    - 三个电机信号脚分配明确(M0 IO30/31、M1 IO28/29、M2 IO46/47)
    - 上拉怎么加(首选内部上拉,否则10k到3V3、长线4.7k、绝不5V)
    - 方向一致性(正PWM→计数增,反了对调黄绿;红白对调=电机反转)
    - 消噪:电机两端并 0.1µF 瓷片抑制电刷火花干扰编码器
    - 连接器以卖家线序表为准、别只认色
2026-06-26 docs: 加 TB6612 驱动板详解(澄清两个GND) + 编码器按实物丝印HH-N20-3修正
    - 新增「TB6612 详细接法」：板上引脚排布图(按丝印,GND标粉色) + 每脚接线表
    ★澄清两个GND：板上2~3个GND内部全连通=同一个地,不是逻辑地/功率地分开,
    接任一到系统共地点即可(=开发板地↔电池地的★共地)
    VM=5.5V/VCC=3V3别接反;STBY=IO52(拉低急停,两块并联);两块板汇总
    - 编码器按用户实物电机丝印 HH-N20-3 修正(之前用卖家通用图,C1/C2信号色反了)：
    白=M1/红=M2(电机)、黑=VCC/蓝=GND、绿=C1/黄=C2(信号)；单电机图同步
2026-06-26 test: 单电机桥(M2)+编码器自检固件，状态上屏
    - components/display: 复用 NanoSoul-Alpha 的 ST7701(MIPI-DSI) 点屏 93 条厂商序列
    + DPHY LDO 上电次序 + LVGL port，去掉触摸（本测试无输入）
    - drv_motor: LEDC 20kHz/10bit PWM(IO26) + IN1(IO27)/IN2(IO32)/STBY(IO52)
    - drv_encoder: PCNT ×4 正交解码(IO46/IO47，内部上拉)+到限累加防溢出
    - drv_ina219: I²C1(IO20/21) 探测 0x40，读分流电压算电流，探不到自动跳过
    - test_app: 上电自动循环正反转，屏显 动作/占空/计数/转速/方向/电流
2026-06-26 test(M2自检): 修正交解码 + RPM 稳定化 + 每圈统计, STOP 改主动刹车
    - 修 PCNT B 路 level_action 应为 (KEEP,INVERSE)：之前误写 (INVERSE,KEEP)
    使 A/B 计数互相抵消，ENC 在 0/1 弹；改后正常 ×4 累加(已上板验证累计几千)
    - ENC_COUNTS_PER_REV 改 28 (7PPR×4，电机轴；商家参数页确认 7PPR 开漏)
    - RPM 改独立 100ms 周期采样 + 死区(消零飘) + EMA 平滑
    - 去掉 LVGL 的 %f（其内置 printf 默认不支持→显示 'f'）：RPM 整数、电流 mA 整数
    - 屏加 A/B 实时电平诊断行 + 每圈 F/R/N(正转/反转/净计数) 统计
2026-06-30 pcb: schematic-parity 真零(零 ignore) + 重导 Gerber
    DRC `--schematic-parity --severity-all` = 0 violation / 0 unconnected /
    0 schematic-parity,62 项检查全置 error、零 ignore(旧版的 7 项 ignore 全部真修掉,
    非关检查)。verify_board 65/65、布线 778 走线+60 过孔未动。
    - 修通 circuit-synth 原理图连通性:它把一器件所有网名标签堆在 pin1 → KiCad 推断错网。
    按 .net 逐脚在真实连接点重放 global_label(fix_sch_labels),net_conflict 199→0;
    真 NC 脚在板上配同名 unconnected- 网对齐(assign_nc_nets)。
2026-06-30 pcb: 修嘉立创 SMT 单两处"邮寄/停产"料 — U6→QMI8658A、R9 shunt→1206
    SMT 下单核对单 待邮寄(2): U6 IMU 停产、R9 shunt 无现货。改为全现货可自动贴装：
    - U6 IMU: QMI8658C(C2842151,JLC SMT 停产/邮寄) → 同族 QMI8658A(C3021082,
    现货 39k)。同 LGA-14、4 线 SPI 脚位完全一致(A 版 datasheet 13-52-25
    Table3+Fig4 逐脚核过:1=SDO/4=INT1/5=VDDIO/6,7=GND/8=VDD/12=CS/13=SCL/
    14=SDA,2/3/9/10/11 SPI 下可悬空)、驱动同(SensorLib/Waveshare)→ 板/固件不动,仅换料号。
    - R9 50mΩ 电流采样 shunt: 0805 50mΩ 在 JLC 无现货(UNI-ROYAL C127697 仅 4 颗、
